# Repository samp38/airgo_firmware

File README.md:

# airgo_firmware
[link to project](https://wikilab.myhumankit.org/index.php?title=Projets:Automatisation_Support_Joystick_Menton_Fauteuil_Roulant)

## Mode of operation
This setup mean to drive a retractable arm that hold a joystick needed to stir an electrical weelchair. The arm can be retracted/extended to its end positions or stopped inbetween. The system is composed of :
- a push button big enough to be actuated with the head. (temporary contact, normally open)
- an arduino mini pro (atmega328p in its 3.3v version preferably)
- a DC motor H-Bridge driver (DVR 8838) to drive the linear actuator that moves the arm
- the linear actuator itself, with en of course switches that autmatically open the power circuit when the it reaches its end of course positions

Once assembled, the system works as described :
- a long press will retract the arm
- a double press will extend the arm
- a simple press will stop the arm

The system works on 7.4 Li-Ion battery, but the arduino mini pro is powered by one cell only on its RAW input, to shunt the voltage regulator. You also have to remove the led on the arduino, so it won't draw current during deep sleep. With this setup, we're able to draw 5 uA in deep sleep mode. As the arduino mini pro doesn't have a usb2serial chip, you will have to [program it with an external programmer](https://www.instructables.com/How-to-Program-Arduino-Pro-Mini-Using-Arduino-UNO/) (arduino as isp, ftdi...).

## Firmware specifications
- smart push button with actions linked to different press types (short press, long press and double press)
- deep sleep, wake on external interrupt of the push button
- drive DC motor CW or CCW depending on state
- (optional) motor current monitoring via shunt resistor and avr ADC

## Hardware
- arduino mini pro 8Mhz
- motor driver DVR8838
- [Schematics here](./doc/schematics.pdf)

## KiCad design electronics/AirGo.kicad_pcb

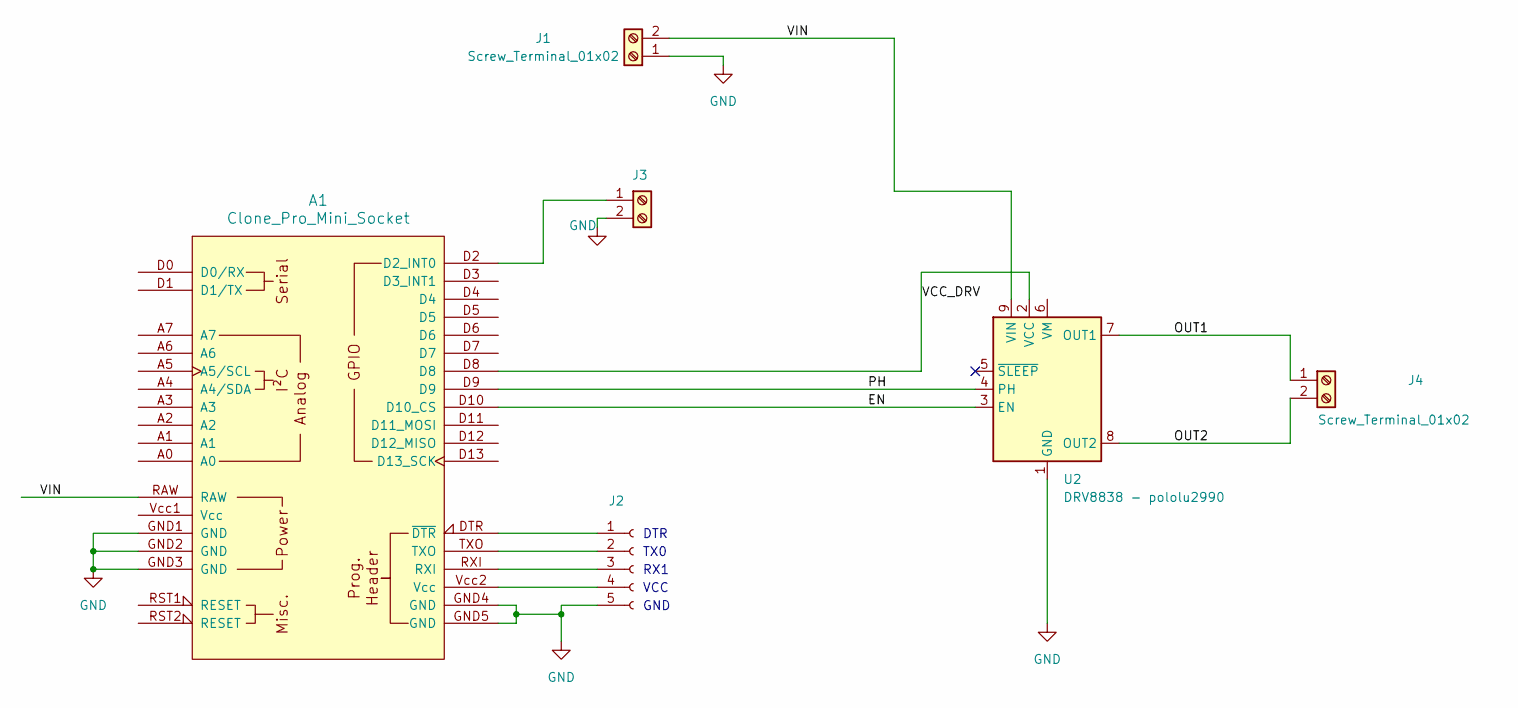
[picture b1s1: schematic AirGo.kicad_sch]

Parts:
A1: Clone_Pro_Mini_Socket
J1, J3, J4: Screw_Terminal_01x02; PinHeader_1x02_P2.54mm_Vertical
J2: Conn_01x05_Socket; PinHeader_1x05_P2.54mm_Vertical
U2: DRV8838 - pololu2990; DIP-10_W7.62mm_LongPads

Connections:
/EN: A1.D10 (D10_CS), U2.3 (EN)
/OUT1: J4.1, U2.7 (OUT1)
/OUT2: J4.2, U2.8 (OUT2)
/PH: A1.D9, U2.4 (PH)
/VCC_DRV: A1.D8, U2.2 (VCC)
/VIN: A1.RAW, J1.2, U2.9 (VIN)
GND: A1.GND1 (GND), A1.GND2 (GND), A1.GND3 (GND), A1.GND4 (GND), A1.GND5 (GND), J1.1, J2.5, J3.2, U2.1 (GND), U2.10 (GND)
unnamed: A1.D2 (D2_INT0), J3.1
unnamed: A1.DTR (~DTR), J2.1
unnamed: A1.TXO, J2.2
unnamed: A1.RXI, J2.3
unnamed: A1.Vcc2 (Vcc), J2.4

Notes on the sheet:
TX0
DTR
VCC
RX1
GND

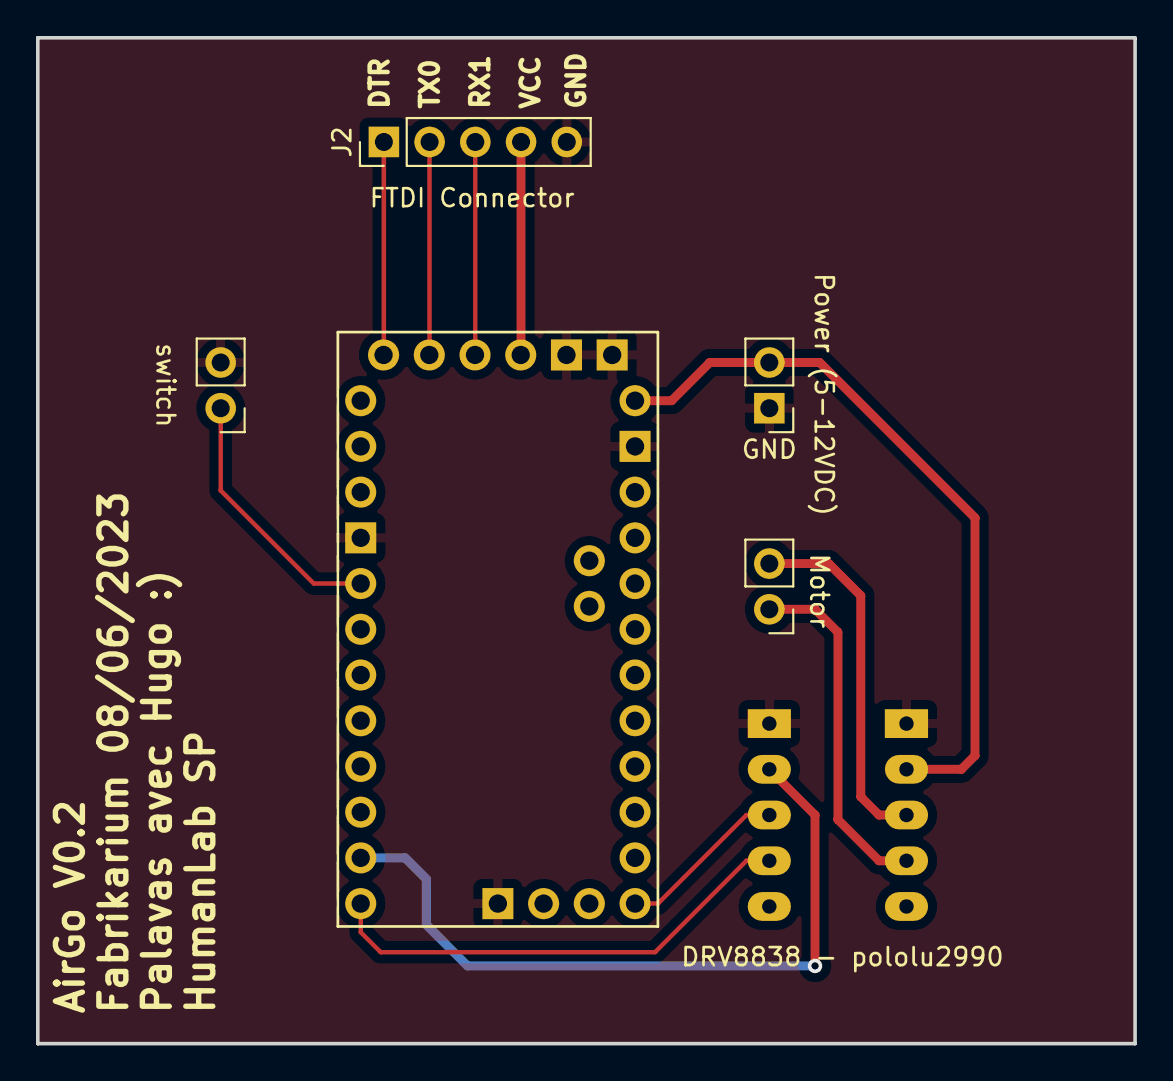
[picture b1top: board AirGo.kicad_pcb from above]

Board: 2 copper layers, 61.0 x 55.9 mm, 6 parts (0 on the bottom side), 12 nets.

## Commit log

2023-06-07 add arduino mini pro pinout image
2023-06-07 amend
2023-06-07 amend again
2023-06-07 add bsp.h to define pins
2023-06-07 forgot ifndef
2023-06-07 add motor & eeprom functions
2023-06-07 Add ISR TODO : timer interrupt to change state and current monitoring
2023-06-07 disable interrupt trigger when running interrupt routine
2023-06-07 run interrupt in loop
2023-06-07 ISP code
2023-06-07 ports specified
2023-06-07 remove global state
2023-06-07 boolean sucks
2023-06-07 Bool is ok when interruptions are handled properly
2023-06-07 add timer1 setup for future timing functions
2023-06-07 create 2 environments for pio
2023-06-07 include lowpower library
2023-06-07 sorry koji
2023-06-07 add deep sleep
2023-06-08 new motor logic + oneButton implementation
2023-06-08 change motor pins for H Bridge DRV8838
2023-06-08 Update motor routines for DRV8838
2023-06-08 remove useless log
2023-06-08 set motor pins mode to output
2023-06-08 stop motor in setup
2023-06-08 stop motor at the end of timer countdown
2023-06-09 add schematics and pcb doc files
2023-06-09 Add Yoann's electronic design
2024-03-21 Fix pcb (edited with Kicad 8.0) and generate gerber & drill files
2024-03-21 Add pcb 3d view with th components
